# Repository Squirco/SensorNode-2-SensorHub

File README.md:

# SensorNode-2-SensorHub
SensorHub files for version 2 of the SensorNode

Firmware files for Squirco Sensor Network Light Switch's SensorHub component, as seen on Hackaday here:  
https://hackaday.io/project/3321-squirco-smart-home-system-sensor-network

#Libraries Used
Arduino libraries used in this project may be modified to fit the project. All credits due to the originators.

https://github.com/sparkfun/SparkFun_BME280_Arduino_Library  
https://github.com/thijse/Arduino-CmdMessenger  
https://github.com/thijse/Arduino-EEPROMEx  
https://github.com/WickedDevice/SoftReset  
https://github.com/PaulStoffregen/TimerOne  

#License Information
Files are released under the MIT License  
Original Design by Steven  
Distributed as-is; no warranty is given

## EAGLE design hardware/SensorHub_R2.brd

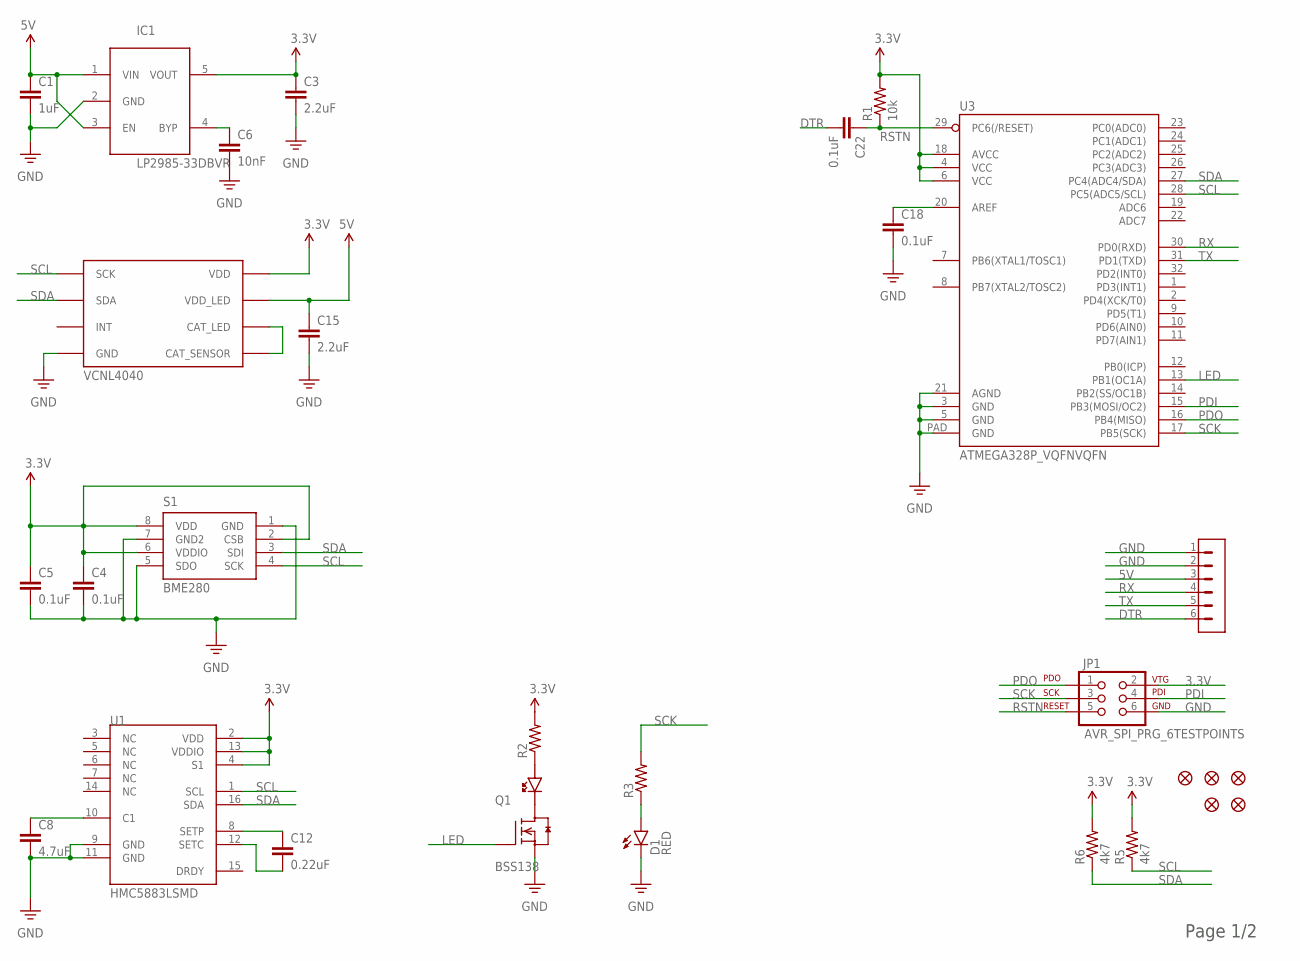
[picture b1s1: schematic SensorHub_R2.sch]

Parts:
C1: 1uF; 0603-CAP
C3, C15: 2.2uF; 0603-CAP
C4, C5, C18, C22: 0.1uF; 0603-CAP
C6: 10nF; 0603-CAP
C8: 4.7uF; 0603-CAP
C12: 0.22uF; 0603-CAP
D1: RED; LED-0603
FID1, FID2, FID3, FID4, FID5: FIDUCIALUFIDUCIAL; MICRO-FIDUCIAL
IC1: LP2985-33DBVR; SOT23-5L
JP1: AVR_SPI_PRG_6TESTPOINTS; 2X3_TEST_POINTS
Q1: BSS138; SOT23
R1: 10k; R0603
R2, R3: RESISTOR0603; 0603-RES
R5, R6: 4k7; R0603
S1: BME280
U1: HMC5883LSMD; 16LPCC
U3: ATMEGA328P_VQFNVQFN; MLF32-PAD
U$1: M06-LONG
U$3: VCNL4040
U$4: PLCC_LED; LED-PLCC

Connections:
3.3V: C3.1, C4.1, C5.1, IC1.5 (VOUT), JP1.2, R1.2, R2.2, R5.2, R6.2, S1.2 (CSB), S1.6 (VDDIO), S1.8 (VDD), U1.2 (VDD), U1.4 (S1), U1.13 (VDDIO), U3.4 (VCC), U3.6 (VCC), U3.18 (AVCC), U$3.3 (VDD)
5V: C1.1, C15.1, IC1.1 (VIN), IC1.3 (EN), U$1.3, U$3.4 (VDD_LED)
DTR: C22.2, U$1.6
GND: C1.2, C3.2, C4.2, C5.2, C6.2, C8.2, C15.2, C18.2, D1.C, IC1.2 (GND), JP1.6, Q1.2 (S), S1.1 (GND), S1.5 (SDO), S1.7 (GND2), U1.9 (GND), U1.11 (GND), U3.3 (GND), U3.5 (GND), U3.21 (AGND), U3.PAD (GND), U$1.1, U$1.2, U$3.1 (GND)
LED: Q1.1 (G), U3.13 (PB1(OC1A))
unnamed: Q1.3 (D), U$4.CATHODE
unnamed: R2.1, U$4.ANODE
unnamed: D1.A, R3.1
unnamed: C6.1, IC1.4 (BYP)
unnamed: U$3.2 (CAT_SENSOR), U$3.5 (CAT_LED)
unnamed: C18.1, U3.20 (AREF)
unnamed: C8.1, U1.10 (C1)
unnamed: C12.1, U1.8 (SETP)
unnamed: C12.2, U1.12 (SETC)
PDI: JP1.4, U3.15 (PB3(MOSI/OC2))
PDO: JP1.1, U3.16 (PB4(MISO))
RSTN: C22.1, JP1.5, R1.1, U3.29 (PC6(/RESET))
RX: U3.30 (PD0(RXD)), U$1.4
SCK: JP1.3, R3.2, U3.17 (PB5(SCK))
SCL: R5.1, S1.4 (SCK), U1.1 (SCL), U3.28 (PC5(ADC5/SCL)), U$3.8 (SCK)
SDA: R6.1, S1.3 (SDI), U1.16 (SDA), U3.27 (PC4(ADC4/SDA)), U$3.7 (SDA)
TX: U3.31 (PD1(TXD)), U$1.5

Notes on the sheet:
Page 1/2

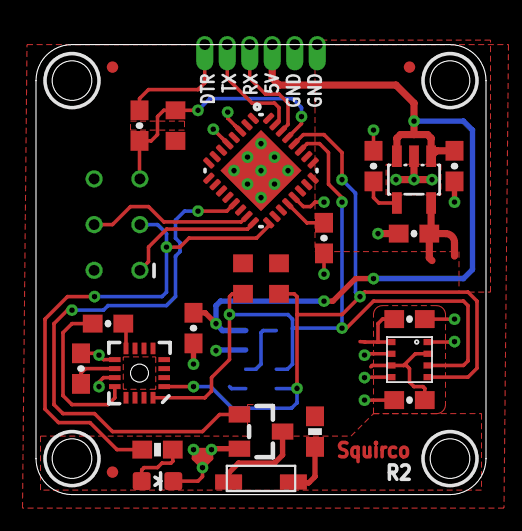
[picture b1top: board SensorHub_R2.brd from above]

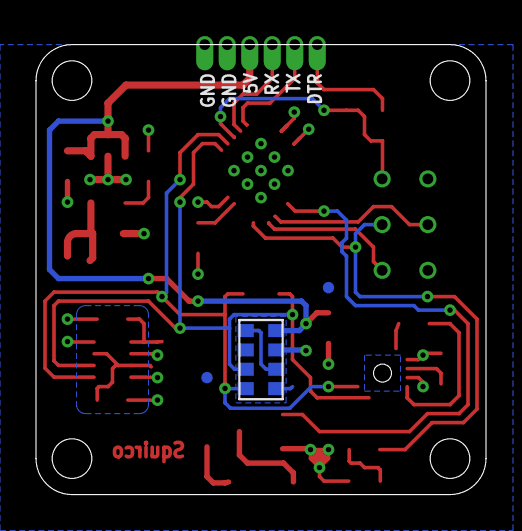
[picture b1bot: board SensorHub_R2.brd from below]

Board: 2 copper layers, 25.0 x 25.0 mm, 30 parts (3 on the bottom side), 22 nets.

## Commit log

2016-07-08 :boom::camel: Added .gitattributes
2016-07-08 test
2016-07-08 Revert "initial commit"
    This reverts commit 9bf99cc8278f894912d5415088cf907da0cc734c.
2016-07-08 Revert "Revert "initial commit""
    This reverts commit 463ea5dc7f296b845244930672938ee25dd86d2a.
2016-07-08 Removed garbage files
2016-07-14 added night light mode "undo"
    added 1 step night light mode change "undo"
2016-07-20 bug fixes
2016-08-08 bug fix
2016-08-15 bug fixes and general improvements
    added feedback after saving settings in eeprom
2016-08-17 reorganized directory
2016-08-18 Added hardware files
2016-08-19 added periodic proximity reporting
2016-08-25 Updated proximity sensor calibration code
2016-08-25 updated versioning
2016-08-25 bug fix
    Fixed a bug where switching from ALS mode to PS_ALS mode while the led
    was on wouldn't turn itself off.
2016-09-13 change default data report interval to 10s from 20s

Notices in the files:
parts and their libraries:
SparkFun-Capacitors: Licensing: Creative Commons ShareAlike 4.0 International - https://creativecommons.org/licenses/by-sa/4.0
m-pad-2.1: License : GNU General Public License version 2 (see bottom)
